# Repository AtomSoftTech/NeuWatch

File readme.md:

An ArduinoZero compatible watch with extra Features:<br>
<br>
ADXL335 Accelerometer<br>
MCP73831 - Lipo Charger<br>
Custom battery sense circuit<br>
Oled and MicroSD stack on PCB <br>
HC06 Bluetooth<br>
Cool side buttons<br>
<br>
Will be programable via Arduino IDE as the Zero (native)

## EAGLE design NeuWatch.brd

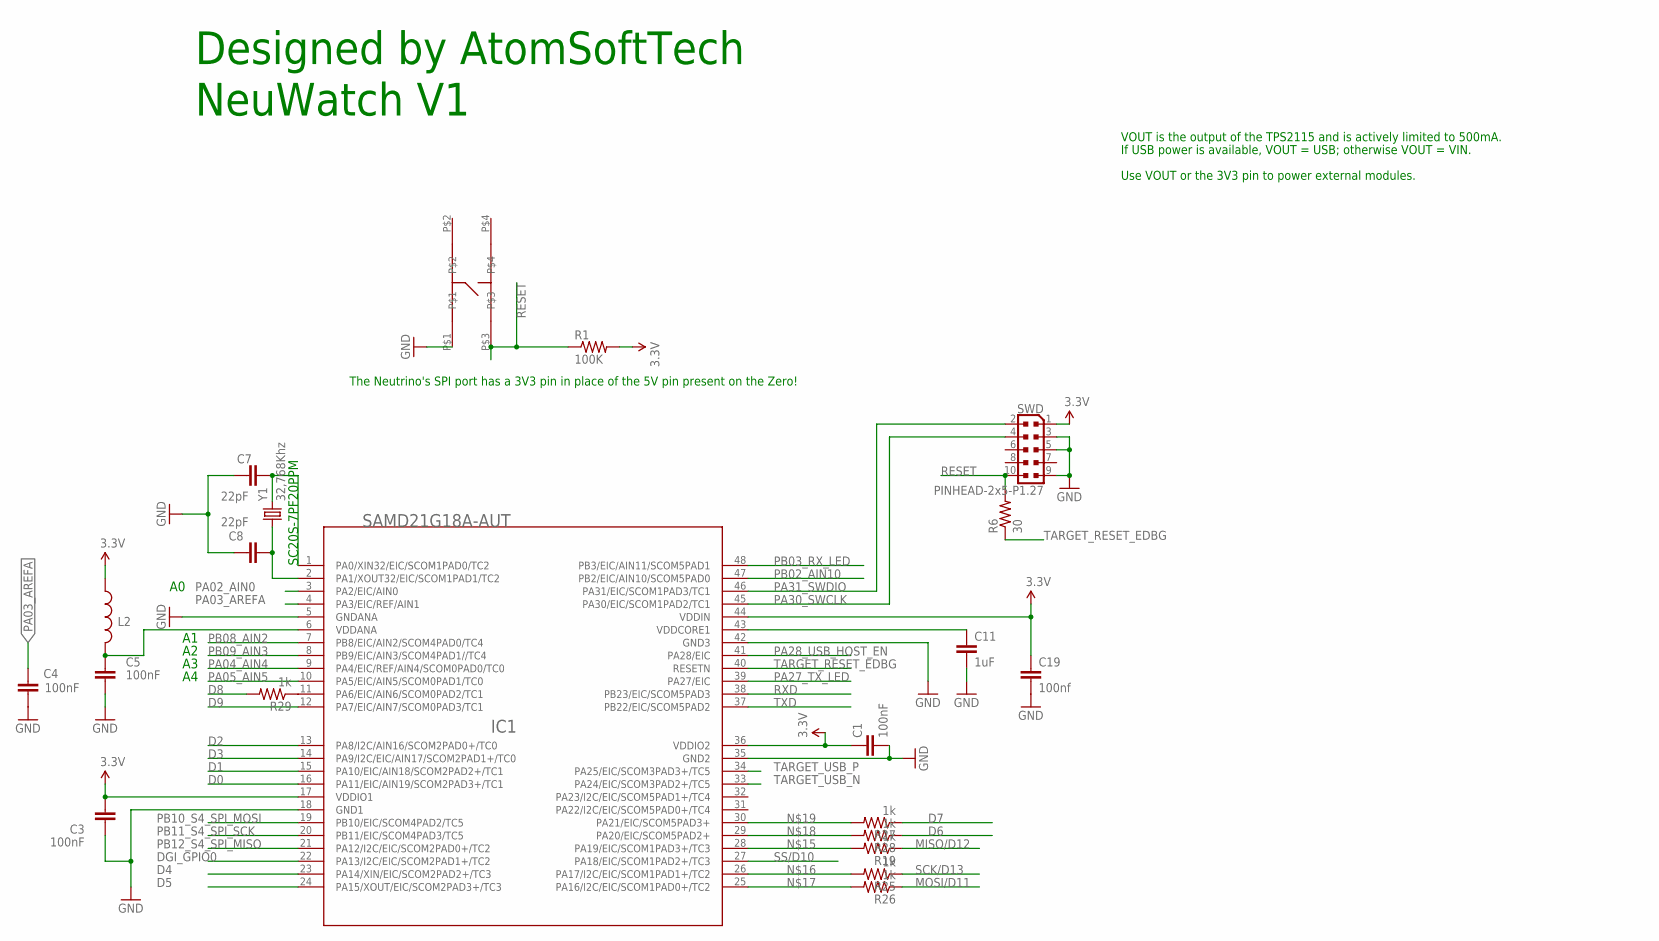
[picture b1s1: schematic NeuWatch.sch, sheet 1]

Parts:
C1, C3, C4, C5: 100nF; C0402
C7, C8: 22pF; C0402
C11: 1uF; C0402
C19: 100nf; C0402
IC1: SAMD21G18A-AUT; INTEGRATEDCIRCUITS_TQFP48-7X7
L2: INDUCTOR0603-TDK; 0603-TDK
R1: 100K; R0402
R6: 30; R0402
R19, R25, R26, R27, R28, R29: 1k; R0402
RESET: TACTILE_SWITCH; PTS540
SWD: PINHEAD-2x5-P1.27; ARDUINO-NEUTRINO-082_CONNETTORI_PINHEAD-2X5-P127
Y1: 32,768Khz; CRYSTAL-SMD-2.0X1.2

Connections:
3.3V: C1.1, C3.2, C19.1, IC1.17 (VDDIO1), IC1.36 (VDDIO2), IC1.44 (VDDIN), L2.1, R1.2, SWD.1; also elsewhere on the board
D0: IC1.16 (PA11/EIC/AIN19/SCOM2PAD3+/TC1); also elsewhere on the board
D1: IC1.15 (PA10/EIC/AIN18/SCOM2PAD2+/TC1); also elsewhere on the board
D2: IC1.13 (PA8/I2C/AIN16/SCOM2PAD0+/TC0); also elsewhere on the board
D3: IC1.14 (PA9/I2C/EIC/AIN17/SCOM2PAD1+/TC0); also elsewhere on the board
D4: IC1.23 (PA14/XIN/EIC/SCOM2PAD2+/TC3); also elsewhere on the board
D5: IC1.24 (PA15/XOUT/EIC/SCOM2PAD3+/TC3); also elsewhere on the board
D6: R28.1; also elsewhere on the board
D7: R27.1; also elsewhere on the board
D8: R29.2; also elsewhere on the board
D9: IC1.12 (PA7/EIC/AIN7/SCOM0PAD3/TC1); also elsewhere on the board
DGI_GPIO0: IC1.22 (PA13/I2C/EIC/SCOM2PAD1+/TC2)
GND: C1.2, C3.1, C4.2, C5.2, C7.1, C8.1, C11.2, C19.2, IC1.5 (GNDANA), IC1.18 (GND1), IC1.35 (GND2), IC1.42 (GND3), RESET.P$1, SWD.3, SWD.5, SWD.9; also elsewhere on the board
MISO/D12: R19.1; also elsewhere on the board
MOSI/D11: R26.1; also elsewhere on the board
unnamed: IC1.28 (PA19/EIC/SCOM1PAD3+/TC3), R19.2
unnamed: IC1.26 (PA17/I2C/EIC/SCOM1PAD1+/TC2), R25.2
unnamed: IC1.25 (PA16/I2C/EIC/SCOM1PAD0+/TC2), R26.2
unnamed: IC1.29 (PA20/EIC/SCOM5PAD2+), R28.2
unnamed: IC1.30 (PA21/EIC/SCOM5PAD3+), R27.2
unnamed: IC1.11 (PA6/EIC/AIN6/SCOM0PAD2/TC1), R29.1
PA00_XIN32: C7.2, IC1.1 (PA0/XIN32/EIC/SCOM1PAD0/TC2), Y1.2
PA01_XOUT32: C8.2, IC1.2 (PA1/XOUT32/EIC/SCOM1PAD1/TC2), Y1.1
PA02_AIN0: IC1.3 (PA2/EIC/AIN0); also elsewhere on the board
PA03_AREFA: C4.1, IC1.4 (PA3/EIC/REF/AIN1)
PA04_AIN4: IC1.9 (PA4/EIC/REF/AIN4/SCOM0PAD0/TC0); also elsewhere on the board
PA05_AIN5: IC1.10 (PA5/EIC/AIN5/SCOM0PAD1/TC0); also elsewhere on the board
PA27_TX_LED: IC1.39 (PA27/EIC)
PA28_USB_HOST_EN: IC1.41 (PA28/EIC); also elsewhere on the board
PA30_SWCLK: IC1.45 (PA30/EIC/SCOM1PAD2/TC1), SWD.4
PA31_SWDIO: IC1.46 (PA31/EIC/SCOM1PAD3/TC1), SWD.2
PB02_AIN10: IC1.47 (PB2/EIC/AIN10/SCOM5PAD0); also elsewhere on the board
PB03_RX_LED: IC1.48 (PB3/EIC/AIN11/SCOM5PAD1)
PB08_AIN2: IC1.7 (PB8/EIC/AIN2/SCOM4PAD0/TC4); also elsewhere on the board
PB09_AIN3: IC1.8 (PB9/EIC/AIN3/SCOM4PAD1//TC4); also elsewhere on the board
PB10_S4_SPI_MOSI: IC1.19 (PB10/EIC/SCOM4PAD2/TC5)
PB11_S4_SPI_SCK: IC1.20 (PB11/EIC/SCOM4PAD3/TC5)
PB12_S4_SPI_MISO: IC1.21 (PA12/I2C/EIC/SCOM2PAD0+/TC2)
RESET: R1.1, R6.2, RESET.P$3, SWD.10
RXD: IC1.38 (PB23/EIC/SCOM5PAD3)
SCK/D13: R25.1; also elsewhere on the board
SS/D10: IC1.27 (PA18/EIC/SCOM1PAD2+/TC3); also elsewhere on the board
TARGET_RESET_EDBG: IC1.40 (RESETN), R6.1
TARGET_USB_N: IC1.33 (PA24/EIC/SCOM3PAD2+/TC5); also elsewhere on the board
TARGET_USB_P: IC1.34 (PA25/EIC/SCOM3PAD3+/TC5); also elsewhere on the board
TXD: IC1.37 (PB22/EIC/SCOM5PAD2)
VDDANA: C5.1, IC1.6 (VDDANA), L2.2
VDDCORE: C11.1, IC1.43 (VDDCORE1)

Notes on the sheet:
The Neutrino's SPI port has a 3V3 pin in place of the 5V pin present on the Zero!
VOUT is the output of the TPS2115 and is actively limited to 500mA.
If USB power is available, VOUT = USB; otherwise VOUT = VIN.
Use VOUT or the 3V3 pin to power external modules.
Designed by AtomSoftTech
NeuWatch V1
SC20S-7PF20PPM

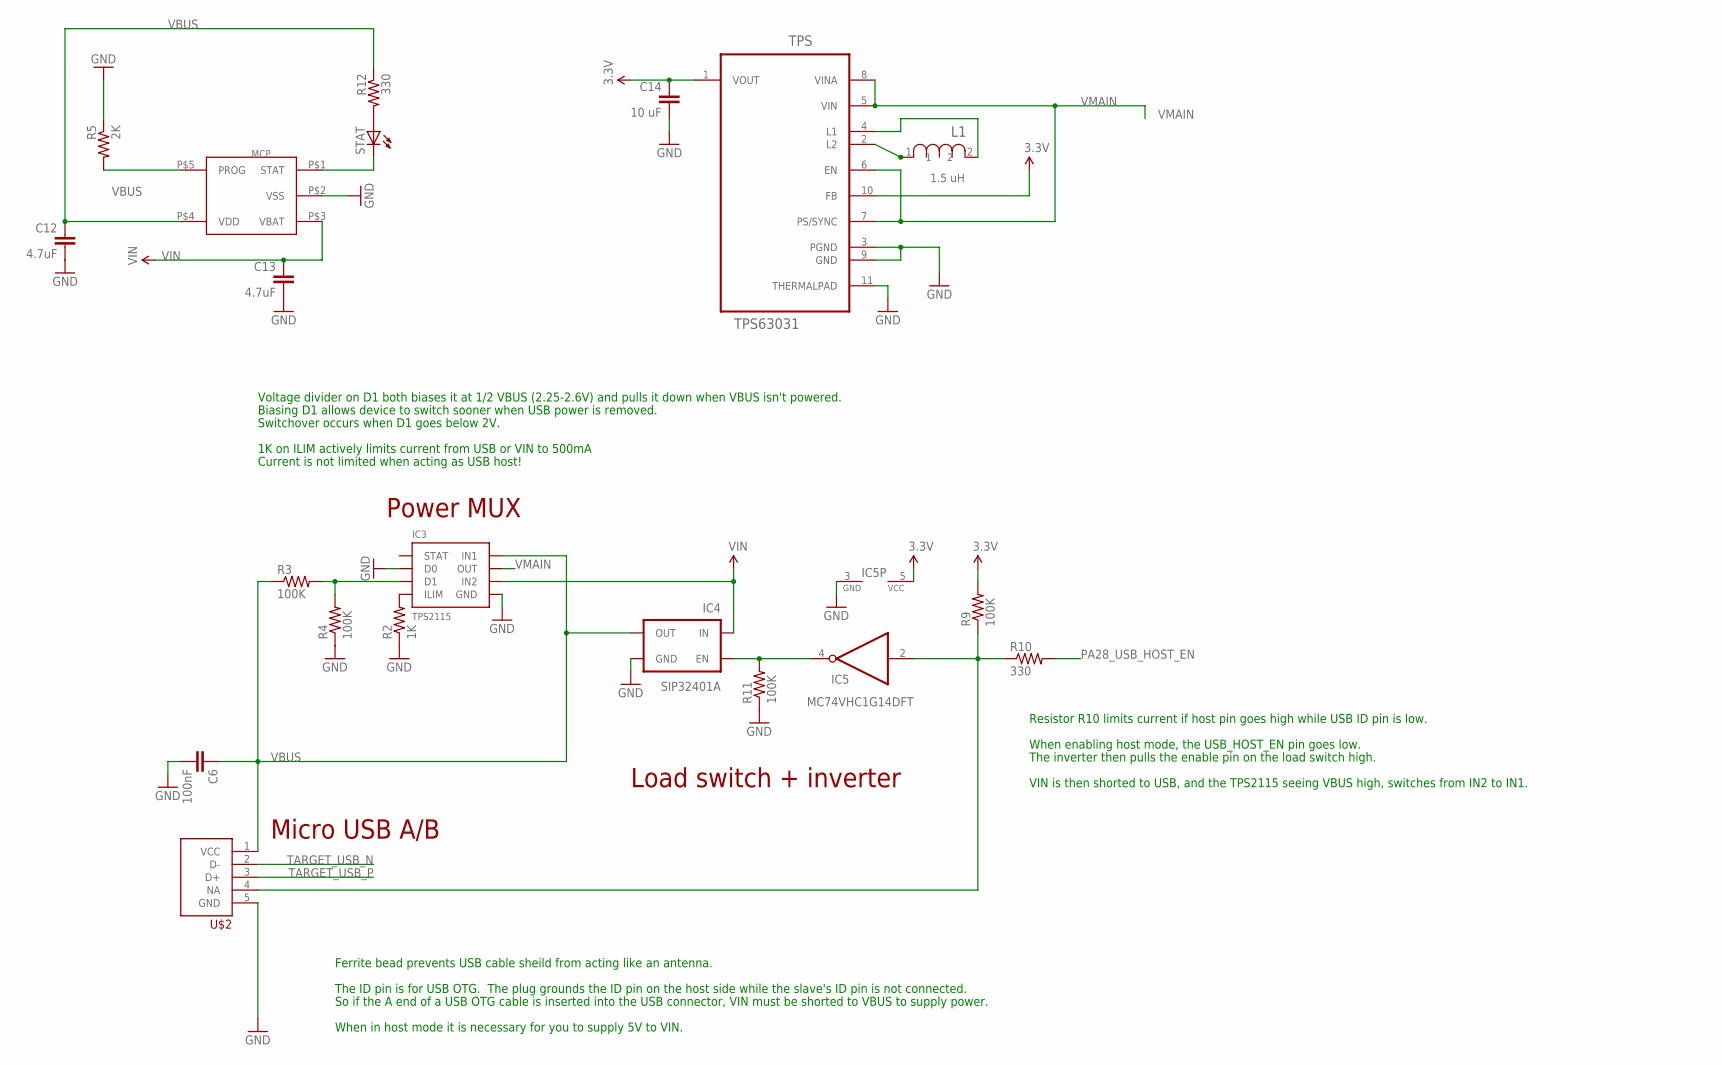
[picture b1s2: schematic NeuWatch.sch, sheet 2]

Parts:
C6: 100nF; C0402
C12, C13: 4.7uF; C0402
C14: 10 uF; C0402
IC3: TPS2115; 8-VDFN
IC4: SIP32401A; TDFN4
IC5: MC74VHC1G14DFT; SC70-5
L1: 1.5 uH; INDC1610X12N
MCP: MCP73831; 5PIN_SOT23
R2: 1K; R0402
R3, R4, R9, R11: 100K; R0402
R5: 2K; R0402
R10, R12: 330; R0402
STAT: LEDSML0603; SML0603
TPS: TPS63031; SON50P260X260X80-11N; MPN TPS63031
U$2: USB_GENERIC_CHEAT; 1LFS

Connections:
3.3V: C14.1, IC5.5 (VCC), R9.2, TPS.1 (VOUT), TPS.10 (FB); also elsewhere on the board
DATT1: IC3.3 (D1), R3.2, R4.2
GND: C6.2, C12.2, C13.2, C14.2, IC3.2 (D0), IC3.5 (GND), IC3.P0 (GND), IC3.V0 (GND), IC3.V1 (GND), IC3.V2 (GND), IC3.V3 (GND), IC3.V4 (GND), IC4.0 (GND), IC4.2 (GND), IC5.3 (GND), MCP.P$2 (VSS), R2.1, R4.1, R5.1, R11.1, TPS.3 (PGND), TPS.9 (GND), TPS.11 (THERMALPAD), U$2.5 (GND); also elsewhere on the board
IC4_EN: IC4.4 (EN), IC5.4 (O), R11.2
ILIM: IC3.4 (ILIM), R2.2
unnamed: L1.1, TPS.2 (L2)
unnamed: MCP.P$1 (STAT), STAT.C
unnamed: MCP.P$5 (PROG), R5.2
unnamed: R12.2, STAT.A
unnamed: L1.2, TPS.4 (L1)
unnamed: IC5.2 (I), R9.1, R10.1, U$2.4 (NA)
PA28_USB_HOST_EN: R10.2; also elsewhere on the board
TARGET_USB_N: U$2.2 (D-); also elsewhere on the board
TARGET_USB_P: U$2.3 (D+); also elsewhere on the board
VBUS: C6.1, C12.1, IC3.8 (IN1), IC4.1 (OUT), MCP.P$4 (VDD), R3.1, R12.1, U$2.1 (VCC)
VIN: C13.1, IC3.6 (IN2), IC4.3 (IN), MCP.P$3 (VBAT); also elsewhere on the board
VMAIN: IC3.7 (OUT), TPS.5 (VIN), TPS.6 (EN), TPS.7 (PS/SYNC), TPS.8 (VINA)

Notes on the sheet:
Micro USB A/B
Ferrite bead prevents USB cable sheild from acting like an antenna.
The ID pin is for USB OTG. The plug grounds the ID pin on the host side while the slave's ID pin is not connected.
So if the A end of a USB OTG cable is inserted into the USB connector, VIN must be shorted to VBUS to supply power.
When in host mode it is necessary for you to supply 5V to VIN.
1K on ILIM actively limits current from USB or VIN to 500mA
Voltage divider on D1 both biases it at 1/2 VBUS (2.25-2.6V) and pulls it down when VBUS isn't powered.
Current is not limited when acting as USB host!
Biasing D1 allows device to switch sooner when USB power is removed.
Switchover occurs when D1 goes below 2V.
When enabling host mode, the USB_HOST_EN pin goes low.
Resistor R10 limits current if host pin goes high while USB ID pin is low.
Load switch + inverter
The inverter then pulls the enable pin on the load switch high.
Power MUX
VIN is then shorted to USB, and the TPS2115 seeing VBUS high, switches from IN2 to IN1.

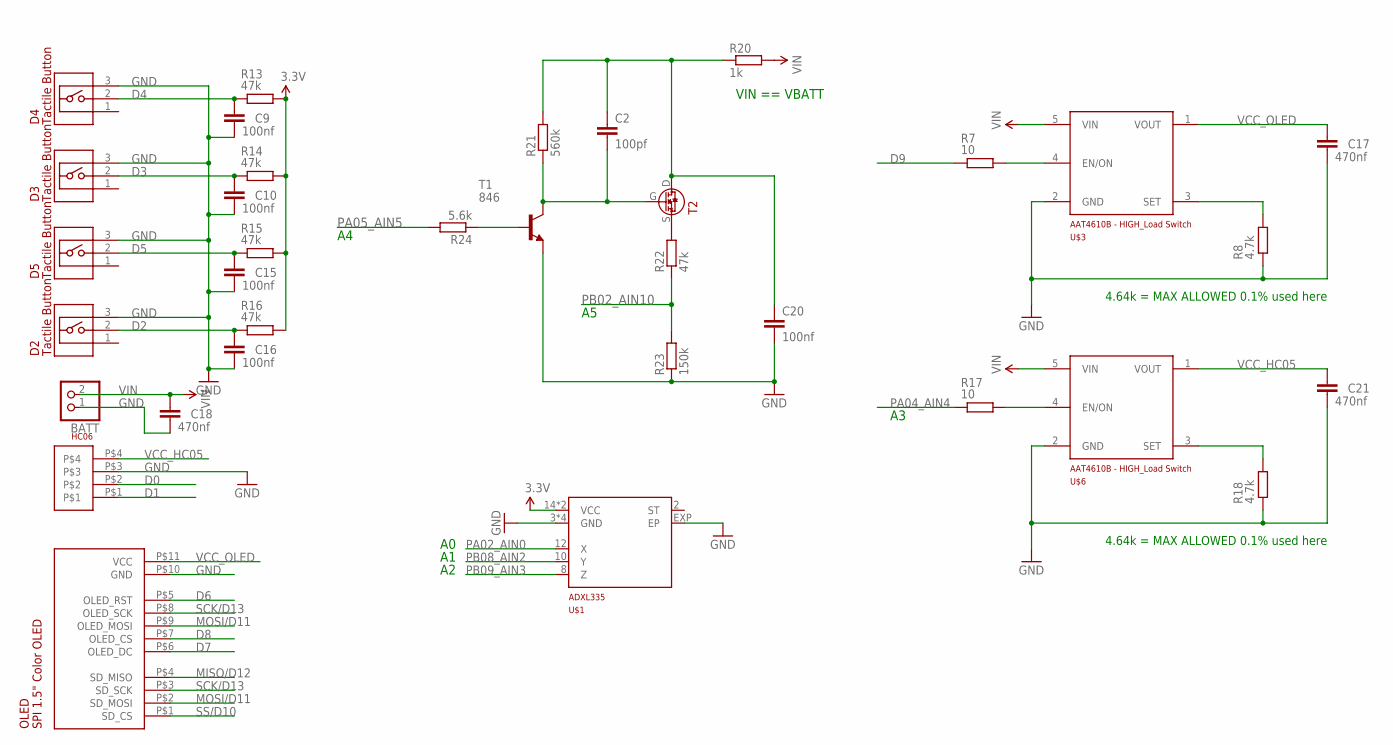
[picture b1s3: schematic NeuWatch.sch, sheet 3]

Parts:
BATT: PINHD-1X2; 1X02
C2: 100pf; C0402
C9, C10, C15, C16, C20: 100nf; C0402
C17, C18, C21: 470nf; C0402
D2, D3, D4, D5: BUTTON_P0; P021301
HC06: 1X4; 1B4
OLED: 1.5-OLED; 1.5OLED
R7, R17: 10; R0402
R8, R18: 4.7k; R0402
R13, R14, R15, R16, R22: 47k; R0402
R20: 1k; R0402
R21: 560k; R0402
R23: 150k; R0402
R24: 5.6k; R0402
T1: 846; SOT23-BEC
T2: 2N7002; MOSFET
U$1: ADXL335; 16LFCSP
U$3, U$6: AAT4610B; SOT23-5

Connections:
3.3V: R13.2, R14.2, R15.2, R16.2, U$1.14 (VCC), U$1.15 (VCC); also elsewhere on the board
D0: HC06.P$2; also elsewhere on the board
D1: HC06.P$1; also elsewhere on the board
D2: C16.1, D2.2, R16.1; also elsewhere on the board
D3: C10.1, D3.2, R14.1; also elsewhere on the board
D4: C9.1, D4.2, R13.1; also elsewhere on the board
D5: C15.1, D5.2, R15.1; also elsewhere on the board
D6: OLED.P$5 (OLED_RST); also elsewhere on the board
D7: OLED.P$6 (OLED_DC); also elsewhere on the board
D8: OLED.P$7 (OLED_CS); also elsewhere on the board
D9: R7.1; also elsewhere on the board
GND: BATT.1, C9.2, C10.2, C15.2, C16.2, C17.2, C18.2, C20.2, C21.2, D2.3, D3.3, D4.3, D5.3, HC06.P$3, OLED.P$10 (GND), R8.1, R18.1, R23.1, T1.E, U$1.3 (GND), U$1.5 (GND), U$1.6 (GND), U$1.7 (GND), U$1.EXP (EP), U$3.2 (GND), U$6.2 (GND); also elsewhere on the board
MISO/D12: OLED.P$4 (SD_MISO); also elsewhere on the board
MOSI/D11: OLED.P$2 (SD_MOSI), OLED.P$9 (OLED_MOSI); also elsewhere on the board
unnamed: C2.2, R21.1, T1.C, T2.G
unnamed: R24.1, T1.B
unnamed: C2.1, C20.1, R20.1, R21.2, T2.D
unnamed: R7.2, U$3.4 (EN/ON)
unnamed: R8.2, U$3.3 (SET)
unnamed: R17.2, U$6.4 (EN/ON)
unnamed: R18.2, U$6.3 (SET)
unnamed: R22.2, T2.S
PA02_AIN0: U$1.12 (X); also elsewhere on the board
PA04_AIN4: R17.1; also elsewhere on the board
PA05_AIN5: R24.2; also elsewhere on the board
PB02_AIN10: R22.1, R23.2; also elsewhere on the board
PB08_AIN2: U$1.10 (Y); also elsewhere on the board
PB09_AIN3: U$1.8 (Z); also elsewhere on the board
SCK/D13: OLED.P$3 (SD_SCK), OLED.P$8 (OLED_SCK); also elsewhere on the board
SS/D10: OLED.P$1 (SD_CS); also elsewhere on the board
VCC_HC05: C21.1, HC06.P$4, U$6.1 (VOUT)
VCC_OLED: C17.1, OLED.P$11 (VCC), U$3.1 (VOUT)
VIN: BATT.2, C18.1, R20.2, U$3.5 (VIN), U$6.5 (VIN); also elsewhere on the board

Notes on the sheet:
VIN == VBATT
4.64k = MAX ALLOWED 0.1% used here

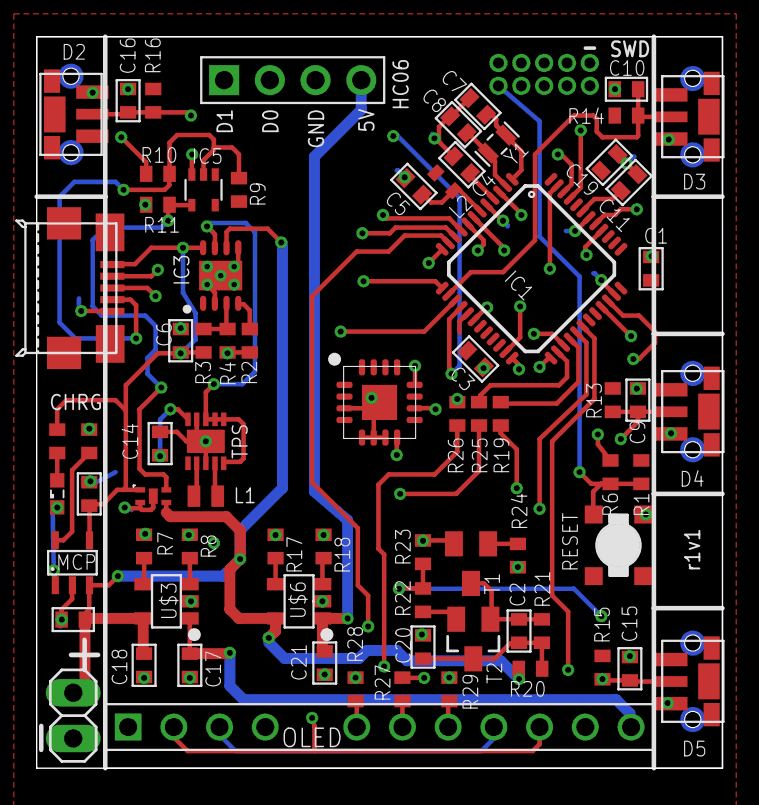
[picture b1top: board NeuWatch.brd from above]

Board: 4 copper layers, 38.1 x 40.6 mm, 75 parts (0 on the bottom side), 62 nets.

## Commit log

2015-07-23 :circus_tent: Added .gitattributes & .gitignore files
2015-07-23 first
    fixed TPS buck
2015-07-23 labels
2015-07-23 readme
2015-07-25 added batsense
2015-07-25 render
2015-07-25 Fixes
    I2C removed and resistors for buttons changed.
2015-07-26 small fixes
2015-07-26 via fix
2015-07-26 text
2015-07-26 batt silk
2015-07-26 updated silk
2015-07-30 removed boost and others
2015-07-30 pinout fixed
2015-07-30 high side load
    for OLED and UART cutoff
2015-07-30 fixes
2015-07-30 redesign
2015-08-01 vin control
2015-08-01 traced
2015-08-03 CLR SPI
    Current Limiting Resistors added to SPI
2015-08-03 silk
2015-08-05 added CLR again
2015-08-08 power traces thicker
2015-08-26 info
2015-08-29 R6 fix

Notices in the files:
parts and their libraries:
SparkFun-FreqCtrl: Licensing: Creative Commons ShareAlike 4.0 International - https://creativecommons.org/licenses/by-sa/4.0
